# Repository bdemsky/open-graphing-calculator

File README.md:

# Open Graphing Calculator

An open-source graphing calculator: an STM32H743 board with a 3.2" IPS touch display, a full symbolic CAS,
2D (textbook) math, graphing, statistics, matrices, solvers, finance, base-n, units and an RPN mode, and a
3D-printed case. The firmware also runs in a macOS simulator and in the browser.

**[Try it in your browser](https://bdemsky.github.io/open-graphing-calculator/)**: the real firmware, compiled
to WebAssembly, nothing to install.

## The board

| Top | Bottom | With Screen |
|---|---|---|
|  |  |  |

The board was designed by Claude, from the block diagram and part choices to the schematic, placement and
routing (with the Freerouting autorouter and its own finishing passes), all generated by scripts in
[`hardware/gen/`](hardware/gen/) into a KiCad project
([`hardware/kicad/`](hardware/kicad/)). The three boards built so far worked on first power-up, with no
rework. Above, a rev A board as it comes from JLCPCB, still with its panel rails. The
top carries the MCU, the SDRAM, the display connector, the microSD socket, USB-C, the debug headers and the 50
key switches; the bottom, the decoupling capacitors and the two holders for the four AAA cells. On the right,
the first power-up with the display taped on.

## Try it in your browser

**[Open the calculator](https://bdemsky.github.io/open-graphing-calculator/)** (GitHub Pages; with every
module installed, so the full CAS, the manual, animation and the rest are there). Click the keys or type on
your keyboard; the shortcuts are listed under the calculator. Some things to try:

- Type `integrate(x^2*exp(x),x)` and press Enter: the antiderivative, in textbook form.
- `sum(1/k^2,k,1,inf)` gives π²/6; `solve(x^3-6*x^2+11*x-6=0,x)` gives [1,2,3]; `factor(x^4-1)`.
- F1 (graph), type `sin(x)`, F5: a graph cell in the notebook. ENTER on it opens the full graph screen
  (trace, zoom, CALC).
- F1 (graph), F1 again (3D), type `4*sin(x)*cos(y)`, F5: a 3D surface. ENTER opens it; F3 (view) has
  colour by height, contours and a contour map.
- SHIFT then MENU opens the built-in manual for the screen you are on.

The page is [`firmware/web/dist/calculator.html`](firmware/web/dist/calculator.html), one self-contained
file: download it (Raw, then save) to run it offline in any modern browser; it needs no server and no
network. `make web` in `firmware/` rebuilds it ([`firmware/README.md`](firmware/README.md), "Web
simulator"). The page leaves out the Python module, which runs only on the calculator and the simulator.

## Build your own

One calculator is a 4-layer board assembled by JLCPCB, a display, four AAA cells and a 3D-printed PETG case.
Nothing on the board is hand-soldered. Allow about three weeks for parts (the boards and the display both
ship from China) and a weekend for printing and assembly.

| Step | What | Guide |
|---|---|---|
| 1. Order the boards | Upload `hardware/fab/` to JLCPCB: Gerbers, BOM and pick-and-place, PCB and assembly in one order. Use the files exactly as committed: they are the rev A files the working boards were built from. About $30 a board beyond the order's fixed costs; five is a good batch. | [`hardware/ORDER.md`](hardware/ORDER.md) §1 |
| 2. Order the rest | The display (EastRising ER-TFT032IPS-3.2 with the capacitive touch panel, from BuyDisplay), a Raspberry Pi Debug Probe (optional, for debugging), M2 × 3 mm heat-set inserts, M2 × 16 mm screws, AAA cells, PETG filament (white, beige, black), and the face-artwork supplies. | [`hardware/ORDER.md`](hardware/ORDER.md) §2–4 |
| 3. Bring up the board | Inspect it, power it from a current-limited bench supply, flash the bring-up image and run its self-test, then flash the calculator. The prebuilt images are in `firmware/release/`; you don't need to build the firmware. | [`hardware/BRINGUP.md`](hardware/BRINGUP.md), [`firmware/release/FLASHING.md`](firmware/release/FLASHING.md) |
| 4. Print the case | Front, back, battery door and 50 loose keys with inlaid legends. An earlier version was printed and assembled on a 0.4 mm nozzle in PETG; the current shells (no key-mat pegs, corner catches) have not been printed yet. | [`enclosure/README.md`](enclosure/README.md) |
| 5. Assemble | Face artwork (optional), heat-set inserts, keys, display, board, back. | [`enclosure/README.md`](enclosure/README.md) |

You need a soldering iron (for the heat-set inserts), a bench power supply with a current limit, and a
printer that can pause for a filament change (for the key legends). The first flash goes over the board's
USB-C port with dfu-util (ROM bootloader) or over SWD with the Debug Probe and OpenOCD; both are in
`FLASHING.md`.

## What's here

| Directory | Contents |
|---|---|
| [`firmware/`](firmware/README.md) | Firmware, CAS, simulators, help manual, tests, release images. The keyboard layout is [`firmware/keys/layout.py`](firmware/keys/layout.py). |
| [`hardware/`](hardware/ARCHITECTURE.md) | The PCB: the as-built rev A KiCad files and fab outputs, the Python generators, ordering and bring-up guides. |
| [`enclosure/`](enclosure/README.md) | The case, keys and battery door (build123d), slicing scripts, face artwork, print and assembly instructions. |

The keyboard has five soft keys under the display, whose labels change with the screen, and SHIFT and ALPHA
layers printed above the keys. Every key is described once in `firmware/keys/layout.py`, which generates the
firmware key map, the case legends, the web simulator and the key documentation.

## License

MIT ([`LICENSE`](LICENSE)) for everything in this repository (firmware, CAS, tools, the KiCad
design and its generators, the case), except the third-party code and data bundled in
[`firmware/third_party/`](firmware/third_party/README.md) (MicroPython, TinyUSB, CMSIS, KaTeX, the X11
fonts, Kconfiglib), each under its own license in its folder.

The KiCad library has footprints but no 3D models, except the battery holder's (the case's door
check uses it). KiCad opens, checks and exports Gerbers without them; only the 3D viewer shows
bare footprints.

Designed by Claude.

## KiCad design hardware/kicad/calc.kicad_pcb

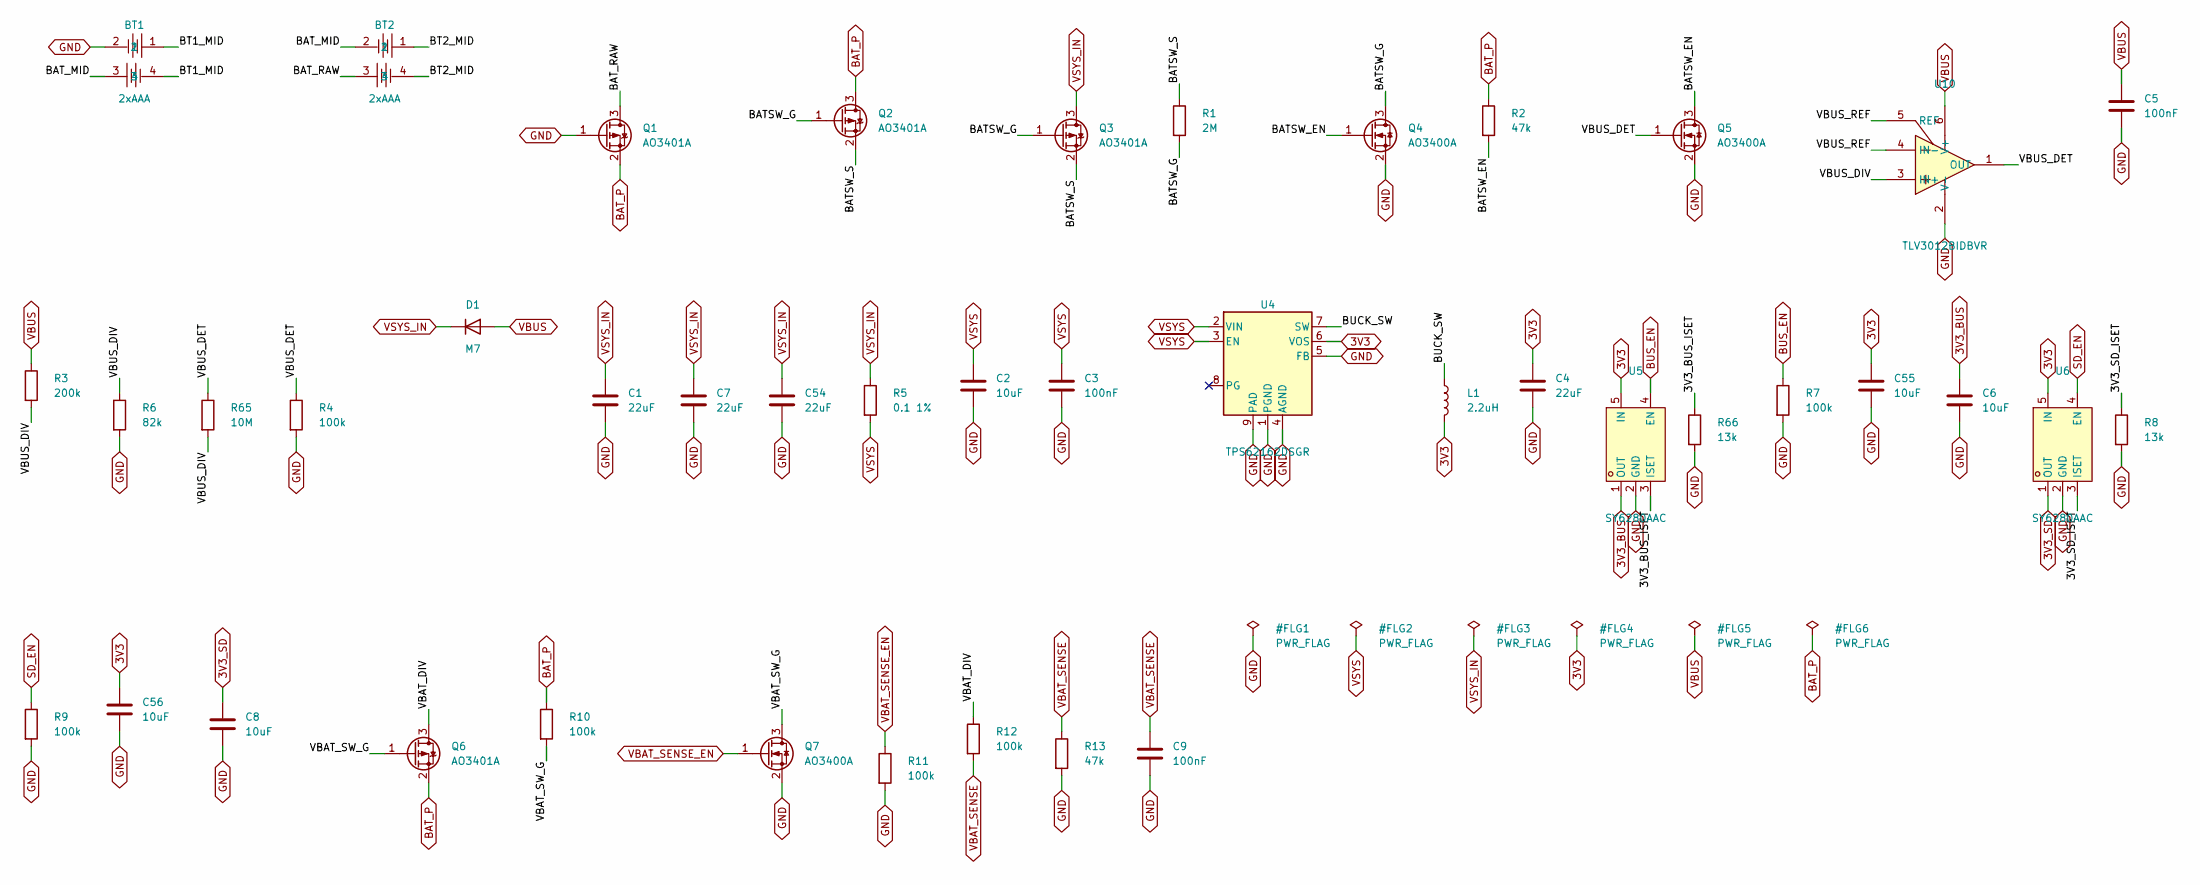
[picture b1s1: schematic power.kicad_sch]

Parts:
BT1, BT2: 2xAAA; BAT-SMD_BH-AAA-B5AA001; LCSC C964881
C1, C4, C7, C54: 22uF; C_0805_2012Metric; LCSC C45783
C2: 10uF; C_0805_2012Metric; LCSC C15850
C3, C5, C9: 100nF; C_0402_1005Metric; LCSC C307331
C6, C8, C55, C56: 10uF; C_0603_1608Metric; LCSC C19702
D1: M7; D_SMA; LCSC C95872
L1: 2.2uH; L_1008_2520Metric; MPN FTC252012S2R2MBCA; LCSC C5832372
Q1, Q2, Q3, Q6: AO3401A; SOT-23; LCSC C15127
Q4, Q5, Q7: AO3400A; SOT-23; LCSC C20917
R1: 2M; R_0603_1608Metric; LCSC C22976
R2, R13: 47k; R_0402_1005Metric; LCSC C25792
R3: 200k; R_0402_1005Metric; LCSC C25764
R4, R7, R9, R10, R11, R12: 100k; R_0402_1005Metric; LCSC C25741
R5: 0.1 1%; R_2512_6332Metric; MPN RLP25FEER100; LCSC C160587
R6: 82k; R_0603_1608Metric; LCSC C23254
R8, R66: 13k; R_0603_1608Metric; LCSC C22797
R65: 10M; R_0603_1608Metric; LCSC C7250
U4: TPS62162DSGR; Texas_DSG0008A_WSON-8-1EP_2x2mm_P0.5mm_EP0.9x1.6mm; LCSC C40256
U5, U6: SY6280AAC; SOT-23-5_L3.0-W1.7-P0.95-LS2.8-BL; LCSC C55136
U10: TLV3012BIDBVR; SOT-23-6_L2.9-W1.7-P0.95-LS2.8-BL; LCSC C20345924

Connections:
3V3: C4.1, C55.1, C56.1, L1.2, U4.6 (VOS), U5.5 (IN), U6.5 (IN); also elsewhere on the board
3V3_BUS: C6.1, U5.1 (OUT); also elsewhere on the board
3V3_SD: C8.1, U6.1 (OUT); also elsewhere on the board
/Power/3V3_BUS_ISET: R66.1, U5.3 (ISET)
/Power/3V3_SD_ISET: R8.1, U6.3 (ISET)
/Power/BATSW_EN: Q4.1 (G), Q5.3 (D), R2.2
/Power/BATSW_G: Q2.1 (G), Q3.1 (G), Q4.3 (D), R1.2
/Power/BATSW_S: Q2.2 (S), Q3.2 (S), R1.1
/Power/BAT_MID: BT1.3, BT2.2
/Power/BAT_RAW: BT2.3, Q1.3 (D)
/Power/BT1_MID: BT1.1, BT1.4
/Power/BT2_MID: BT2.1, BT2.4
/Power/BUCK_SW: L1.1, U4.7 (SW)
/Power/VBAT_DIV: Q6.3 (D), R12.1
/Power/VBAT_SW_G: Q6.1 (G), Q7.3 (D), R10.2
/Power/VBUS_DET: Q5.1 (G), R4.1, R65.1, U10.1 (OUT)
/Power/VBUS_DIV: R3.2, R6.1, R65.2, U10.3 (IN+)
/Power/VBUS_REF: U10.4 (IN-), U10.5 (REF)
BAT_P: Q1.2 (S), Q2.3 (D), Q6.2 (S), R2.1, R10.1; also elsewhere on the board
BUS_EN: R7.1, U5.4 (EN); also elsewhere on the board
GND: BT1.2, C1.2, C2.2, C3.2, C4.2, C5.2, C6.2, C7.2, C8.2, C9.2, C54.2, C55.2, C56.2, Q1.1 (G), Q4.2 (S), Q5.2 (S), Q7.2 (S), R4.2, R6.2, R7.2, R8.2, R9.2, R11.2, R13.2, R66.2, U4.1 (PGND), U4.4 (AGND), U4.5 (FB), U4.9 (PAD), U5.2 (GND), U6.2 (GND), U10.2 (V-); also elsewhere on the board
SD_EN: R9.1, U6.4 (EN); also elsewhere on the board
VBAT_SENSE: C9.1, R12.2, R13.1; also elsewhere on the board
VBAT_SENSE_EN: Q7.1 (G), R11.1; also elsewhere on the board
VBUS: C5.1, D1.2 (A), R3.1, U10.6 (V+); also elsewhere on the board
VSYS: C2.1, C3.1, R5.2, U4.2 (VIN), U4.3 (EN); also elsewhere on the board
VSYS_IN: C1.1, C7.1, C54.1, D1.1 (K), Q3.3 (D), R5.1; also elsewhere on the board

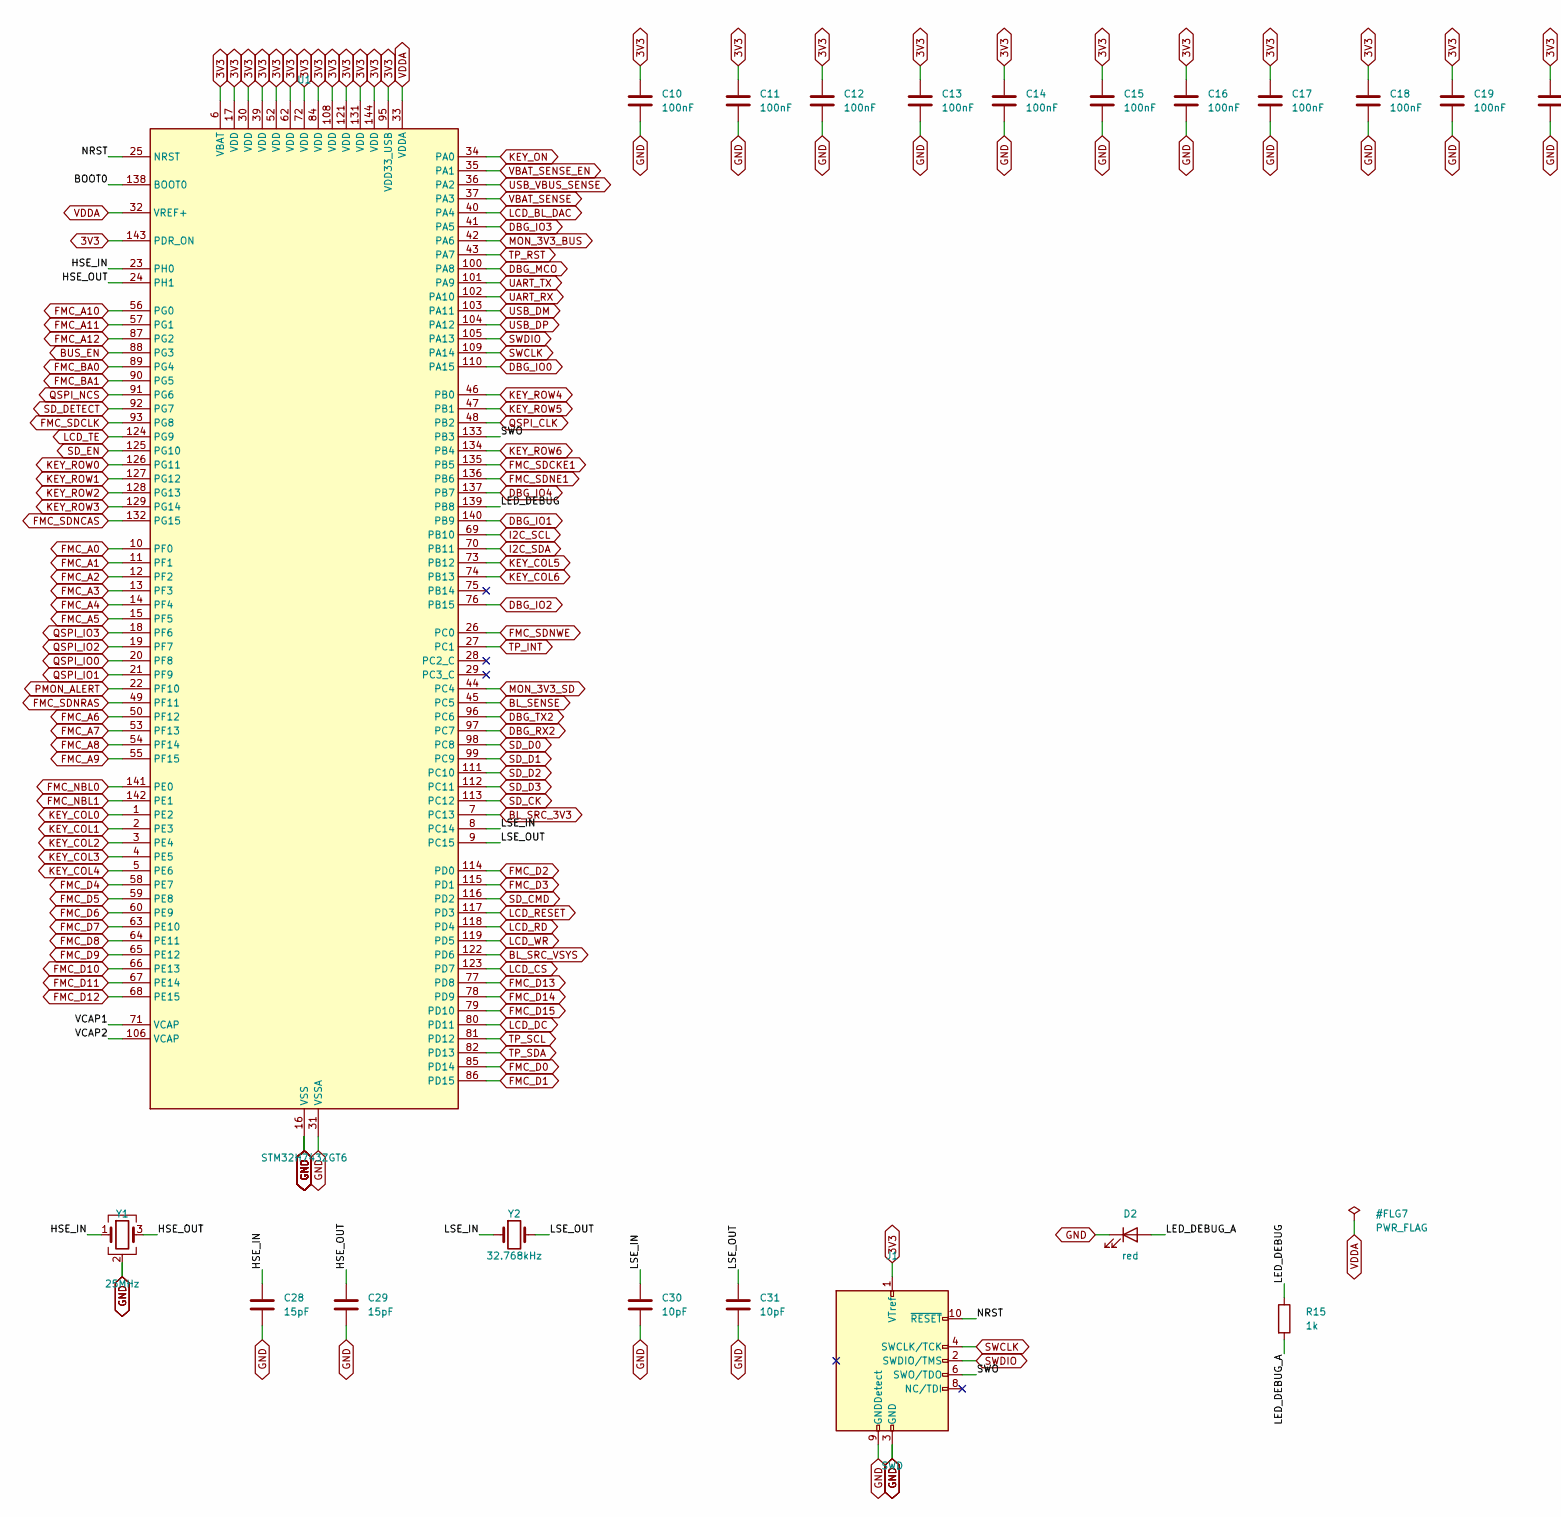
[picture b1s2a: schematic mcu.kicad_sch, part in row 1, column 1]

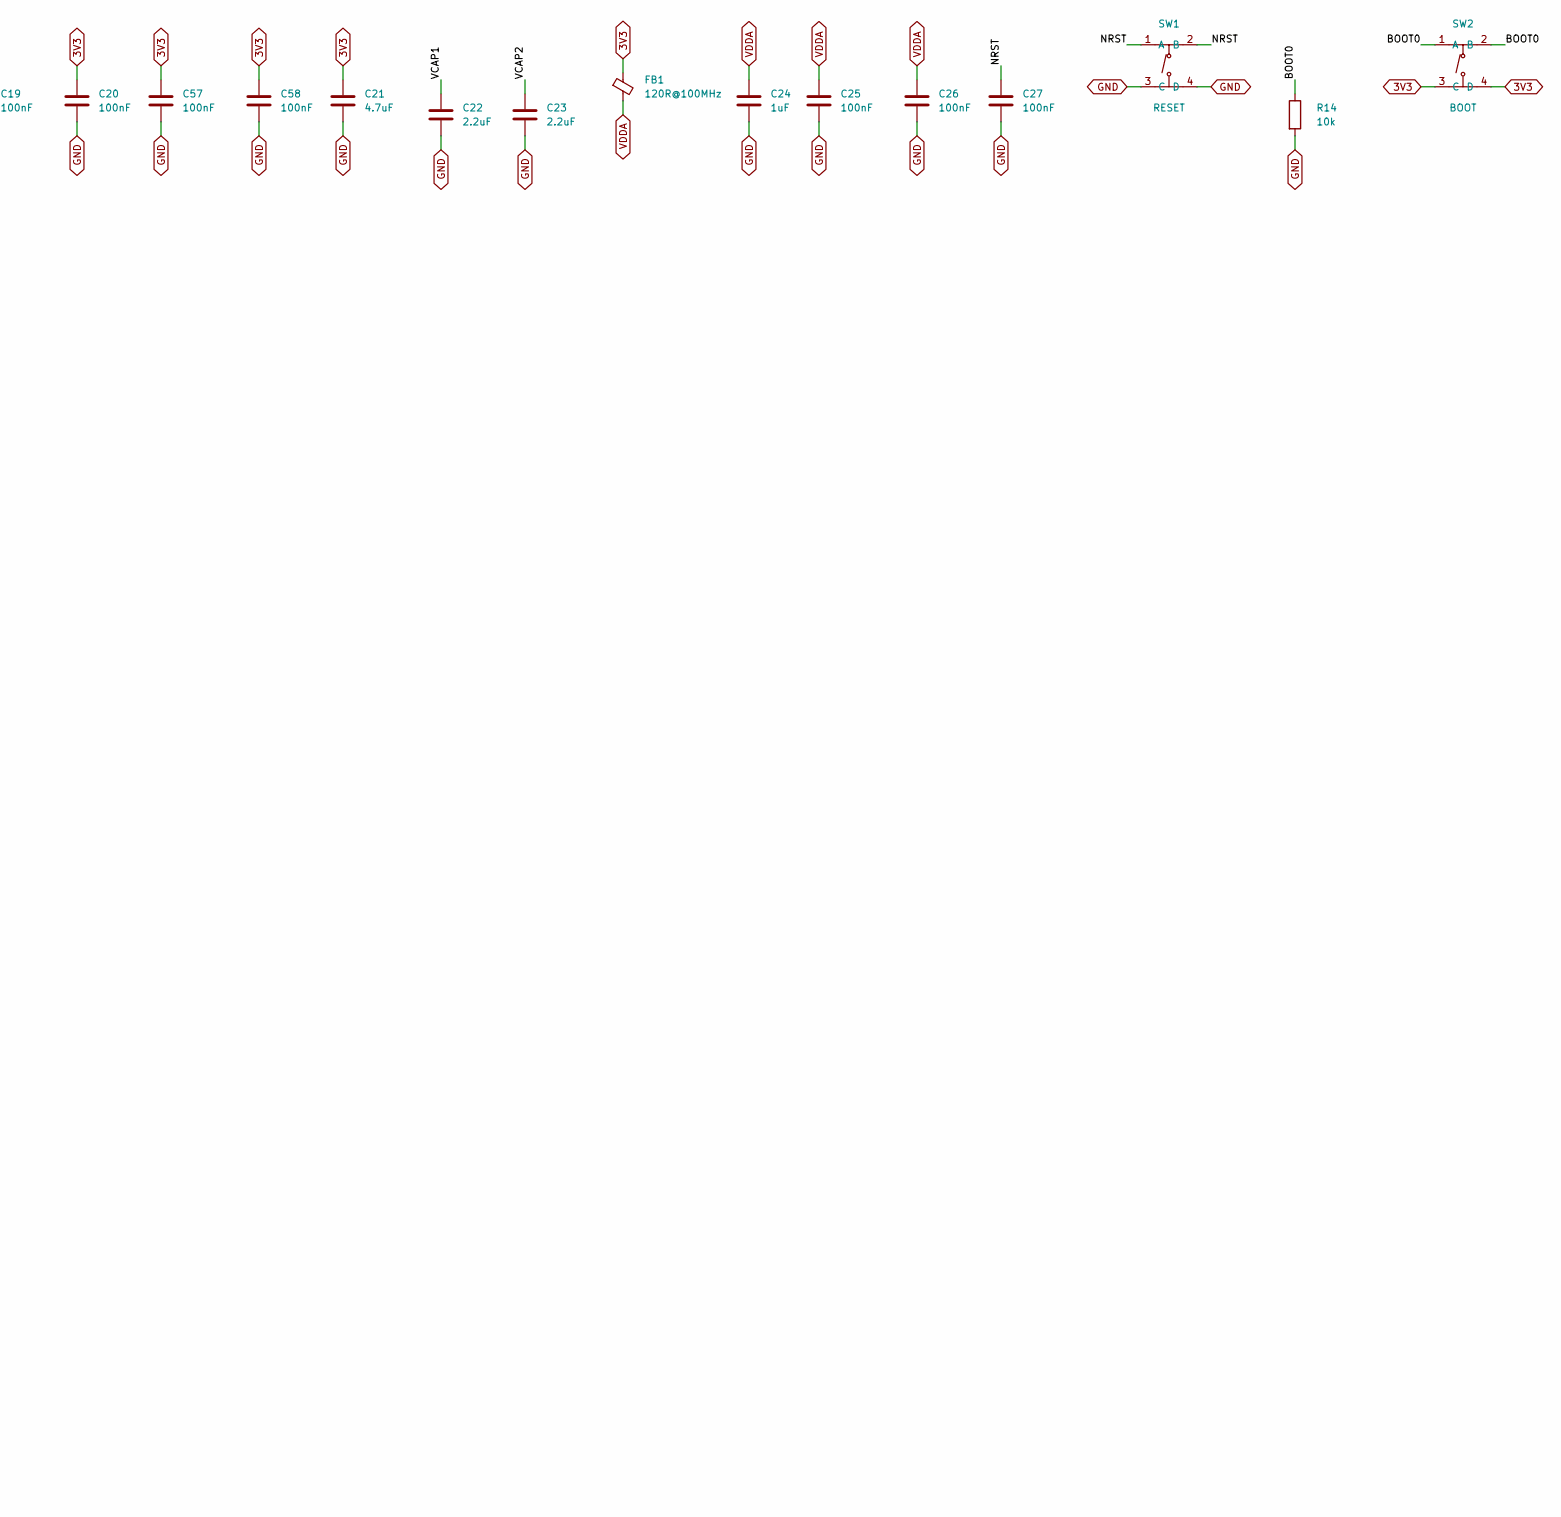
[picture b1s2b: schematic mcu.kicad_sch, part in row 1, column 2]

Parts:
C10, C11, C12, C13, C14, C15, C16, C17, C18, C19, C20, C25, C26, C27, C57, C58: 100nF; C_0402_1005Metric; LCSC C307331
C21: 4.7uF; C_0603_1608Metric; LCSC C19666
C22, C23: 2.2uF; C_0402_1005Metric; LCSC C12530
C24: 1uF; C_0402_1005Metric; LCSC C52923
C28, C29: 15pF; C_0402_1005Metric; LCSC C1548
C30, C31: 10pF; C_0402_1005Metric; LCSC C32949
D2: red; LED_0603_1608Metric; MPN KT-0603R; LCSC C2286
FB1: 120R@100MHz; L_0603_1608Metric; LCSC C14709
J1: SWD; PinHeader_2x05_P1.27mm_Vertical; LCSC C22438120
R14: 10k; R_0402_1005Metric; LCSC C25744
R15: 1k; R_0402_1005Metric; LCSC C11702
SW1: RESET; SW-SMD_4P-L5.1-W5.1-P3.70-LS6.5-TL_H1.5; LCSC C318884
SW2: BOOT; SW-SMD_4P-L5.1-W5.1-P3.70-LS6.5-TL_H1.5; LCSC C318884
U1: STM32H743ZGT6; LQFP-144_20x20mm_P0.5mm; LCSC C730184
Y1: 25MHz; Crystal_SMD_3225-4Pin_3.2x2.5mm; MPN X322525MOB4SI; LCSC C9006
Y2: 32.768kHz; Crystal_SMD_3215-2Pin_3.2x1.5mm; MPN SC-32S 7pF; LCSC C97604

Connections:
3V3: C10.1, C11.1, C12.1, C13.1, C14.1, C15.1, C16.1, C17.1, C18.1, C19.1, C20.1, C21.1, C57.1, C58.1, FB1.1, J1.1 (VTref), SW2.3 (C), SW2.4 (D), U1.6 (VBAT), U1.17 (VDD), U1.30 (VDD), U1.39 (VDD), U1.52 (VDD), U1.62 (VDD), U1.72 (VDD), U1.84 (VDD), U1.95 (VDD33_USB), U1.108 (VDD), U1.121 (VDD), U1.131 (VDD), U1.143 (PDR_ON), U1.144 (VDD); also elsewhere on the board
/MCU/BOOT0: R14.1, SW2.1 (A), SW2.2 (B), U1.138 (BOOT0)
/MCU/HSE_IN: C28.1, U1.23 (PH0), Y1.1
/MCU/HSE_OUT: C29.1, U1.24 (PH1), Y1.3
/MCU/LED_DEBUG: R15.1, U1.139 (PB8)
/MCU/LED_DEBUG_A: D2.2 (A), R15.2
/MCU/LSE_IN: C30.1, U1.8 (PC14), Y2.1
/MCU/LSE_OUT: C31.1, U1.9 (PC15), Y2.2
/MCU/NRST: C27.1, J1.10 (~RESET), SW1.1 (A), SW1.2 (B), U1.25 (NRST)
/MCU/SWO: J1.6 (SWO/TDO), U1.133 (PB3)
/MCU/VCAP1: C22.1, U1.71 (VCAP)
/MCU/VCAP2: C23.1, U1.106 (VCAP)
BL_SENSE: U1.45 (PC5); also elsewhere on the board
BL_SRC_3V3: U1.7 (PC13); also elsewhere on the board
BL_SRC_VSYS: U1.122 (PD6); also elsewhere on the board
BUS_EN: U1.88 (PG3); also elsewhere on the board
DBG_IO0: U1.110 (PA15); also elsewhere on the board
DBG_IO1: U1.140 (PB9); also elsewhere on the board
DBG_IO2: U1.76 (PB15); also elsewhere on the board
DBG_IO3: U1.41 (PA5); also elsewhere on the board
DBG_IO4: U1.137 (PB7); also elsewhere on the board
DBG_MCO: U1.100 (PA8); also elsewhere on the board
DBG_RX2: U1.97 (PC7); also elsewhere on the board
DBG_TX2: U1.96 (PC6); also elsewhere on the board
FMC_A0: U1.10 (PF0); also elsewhere on the board
FMC_A1: U1.11 (PF1); also elsewhere on the board
FMC_A2: U1.12 (PF2); also elsewhere on the board
FMC_A3: U1.13 (PF3); also elsewhere on the board
FMC_A4: U1.14 (PF4); also elsewhere on the board
FMC_A5: U1.15 (PF5); also elsewhere on the board
FMC_A6: U1.50 (PF12); also elsewhere on the board
FMC_A7: U1.53 (PF13); also elsewhere on the board
FMC_A8: U1.54 (PF14); also elsewhere on the board
FMC_A9: U1.55 (PF15); also elsewhere on the board
FMC_A10: U1.56 (PG0); also elsewhere on the board
FMC_A11: U1.57 (PG1); also elsewhere on the board
FMC_A12: U1.87 (PG2); also elsewhere on the board
FMC_BA0: U1.89 (PG4); also elsewhere on the board
FMC_BA1: U1.90 (PG5); also elsewhere on the board
FMC_D0: U1.85 (PD14); also elsewhere on the board
FMC_D1: U1.86 (PD15); also elsewhere on the board
FMC_D2: U1.114 (PD0); also elsewhere on the board
FMC_D3: U1.115 (PD1); also elsewhere on the board
FMC_D4: U1.58 (PE7); also elsewhere on the board
FMC_D5: U1.59 (PE8); also elsewhere on the board
FMC_D6: U1.60 (PE9); also elsewhere on the board
FMC_D7: U1.63 (PE10); also elsewhere on the board
FMC_D8: U1.64 (PE11); also elsewhere on the board
FMC_D9: U1.65 (PE12); also elsewhere on the board
FMC_D10: U1.66 (PE13); also elsewhere on the board
FMC_D11: U1.67 (PE14); also elsewhere on the board
FMC_D12: U1.68 (PE15); also elsewhere on the board
FMC_D13: U1.77 (PD8); also elsewhere on the board
FMC_D14: U1.78 (PD9); also elsewhere on the board
FMC_D15: U1.79 (PD10); also elsewhere on the board
FMC_NBL0: U1.141 (PE0); also elsewhere on the board
FMC_NBL1: U1.142 (PE1); also elsewhere on the board
FMC_SDCKE1: U1.135 (PB5); also elsewhere on the board
FMC_SDCLK: U1.93 (PG8); also elsewhere on the board
FMC_SDNCAS: U1.132 (PG15); also elsewhere on the board
FMC_SDNE1: U1.136 (PB6); also elsewhere on the board
FMC_SDNRAS: U1.49 (PF11); also elsewhere on the board
FMC_SDNWE: U1.26 (PC0); also elsewhere on the board
GND: C10.2, C11.2, C12.2, C13.2, C14.2, C15.2, C16.2, C17.2, C18.2, C19.2, C20.2, C21.2, C22.2, C23.2, C24.2, C25.2, C26.2, C27.2, C28.2, C29.2, C30.2, C31.2, C57.2, C58.2, D2.1 (K), J1.3 (GND), J1.5 (GND), J1.9 (GNDDetect), R14.2, SW1.3 (C), SW1.4 (D), U1.16 (VSS), U1.31 (VSSA), U1.38 (VSS), U1.51 (VSS), U1.61 (VSS), U1.83 (VSS), U1.94 (VSS), U1.107 (VSS), U1.120 (VSS), U1.130 (VSS), Y1.2 (G), Y1.4 (G); also elsewhere on the board
I2C_SCL: U1.69 (PB10); also elsewhere on the board
I2C_SDA: U1.70 (PB11); also elsewhere on the board
KEY_COL0: U1.1 (PE2); also elsewhere on the board
KEY_COL1: U1.2 (PE3); also elsewhere on the board
KEY_COL2: U1.3 (PE4); also elsewhere on the board
KEY_COL3: U1.4 (PE5); also elsewhere on the board
KEY_COL4: U1.5 (PE6); also elsewhere on the board
KEY_COL5: U1.73 (PB12); also elsewhere on the board
KEY_COL6: U1.74 (PB13); also elsewhere on the board
KEY_ON: U1.34 (PA0); also elsewhere on the board
KEY_ROW0: U1.126 (PG11); also elsewhere on the board
KEY_ROW1: U1.127 (PG12); also elsewhere on the board
KEY_ROW2: U1.128 (PG13); also elsewhere on the board
KEY_ROW3: U1.129 (PG14); also elsewhere on the board
KEY_ROW4: U1.46 (PB0); also elsewhere on the board
KEY_ROW5: U1.47 (PB1); also elsewhere on the board
KEY_ROW6: U1.134 (PB4); also elsewhere on the board
LCD_BL_DAC: U1.40 (PA4); also elsewhere on the board
LCD_CS: U1.123 (PD7); also elsewhere on the board
LCD_DC: U1.80 (PD11); also elsewhere on the board
LCD_RD: U1.118 (PD4); also elsewhere on the board
LCD_RESET: U1.117 (PD3); also elsewhere on the board
LCD_TE: U1.124 (PG9); also elsewhere on the board
LCD_WR: U1.119 (PD5); also elsewhere on the board
MON_3V3_BUS: U1.42 (PA6); also elsewhere on the board
MON_3V3_SD: U1.44 (PC4); also elsewhere on the board
PMON_ALERT: U1.22 (PF10); also elsewhere on the board
QSPI_CLK: U1.48 (PB2); also elsewhere on the board
QSPI_IO0: U1.20 (PF8); also elsewhere on the board
QSPI_IO1: U1.21 (PF9); also elsewhere on the board
QSPI_IO2: U1.19 (PF7); also elsewhere on the board
QSPI_IO3: U1.18 (PF6); also elsewhere on the board
QSPI_NCS: U1.91 (PG6); also elsewhere on the board
SD_CK: U1.113 (PC12); also elsewhere on the board
SD_CMD: U1.116 (PD2); also elsewhere on the board
SD_D0: U1.98 (PC8); also elsewhere on the board
SD_D1: U1.99 (PC9); also elsewhere on the board
SD_D2: U1.111 (PC10); also elsewhere on the board
SD_D3: U1.112 (PC11); also elsewhere on the board
SD_DETECT: U1.92 (PG7); also elsewhere on the board
SD_EN: U1.125 (PG10); also elsewhere on the board
SWCLK: J1.4 (SWCLK/TCK), U1.109 (PA14); also elsewhere on the board
SWDIO: J1.2 (SWDIO/TMS), U1.105 (PA13); also elsewhere on the board
TP_INT: U1.27 (PC1); also elsewhere on the board
TP_RST: U1.43 (PA7); also elsewhere on the board
TP_SCL: U1.81 (PD12); also elsewhere on the board
TP_SDA: U1.82 (PD13); also elsewhere on the board
UART_RX: U1.102 (PA10); also elsewhere on the board
UART_TX: U1.101 (PA9); also elsewhere on the board
USB_DM: U1.103 (PA11); also elsewhere on the board
USB_DP: U1.104 (PA12); also elsewhere on the board
USB_VBUS_SENSE: U1.36 (PA2); also elsewhere on the board
VBAT_SENSE: U1.37 (PA3); also elsewhere on the board
VBAT_SENSE_EN: U1.35 (PA1); also elsewhere on the board
VDDA: C24.1, C25.1, C26.1, FB1.2, U1.32 (VREF+), U1.33 (VDDA); also elsewhere on the board

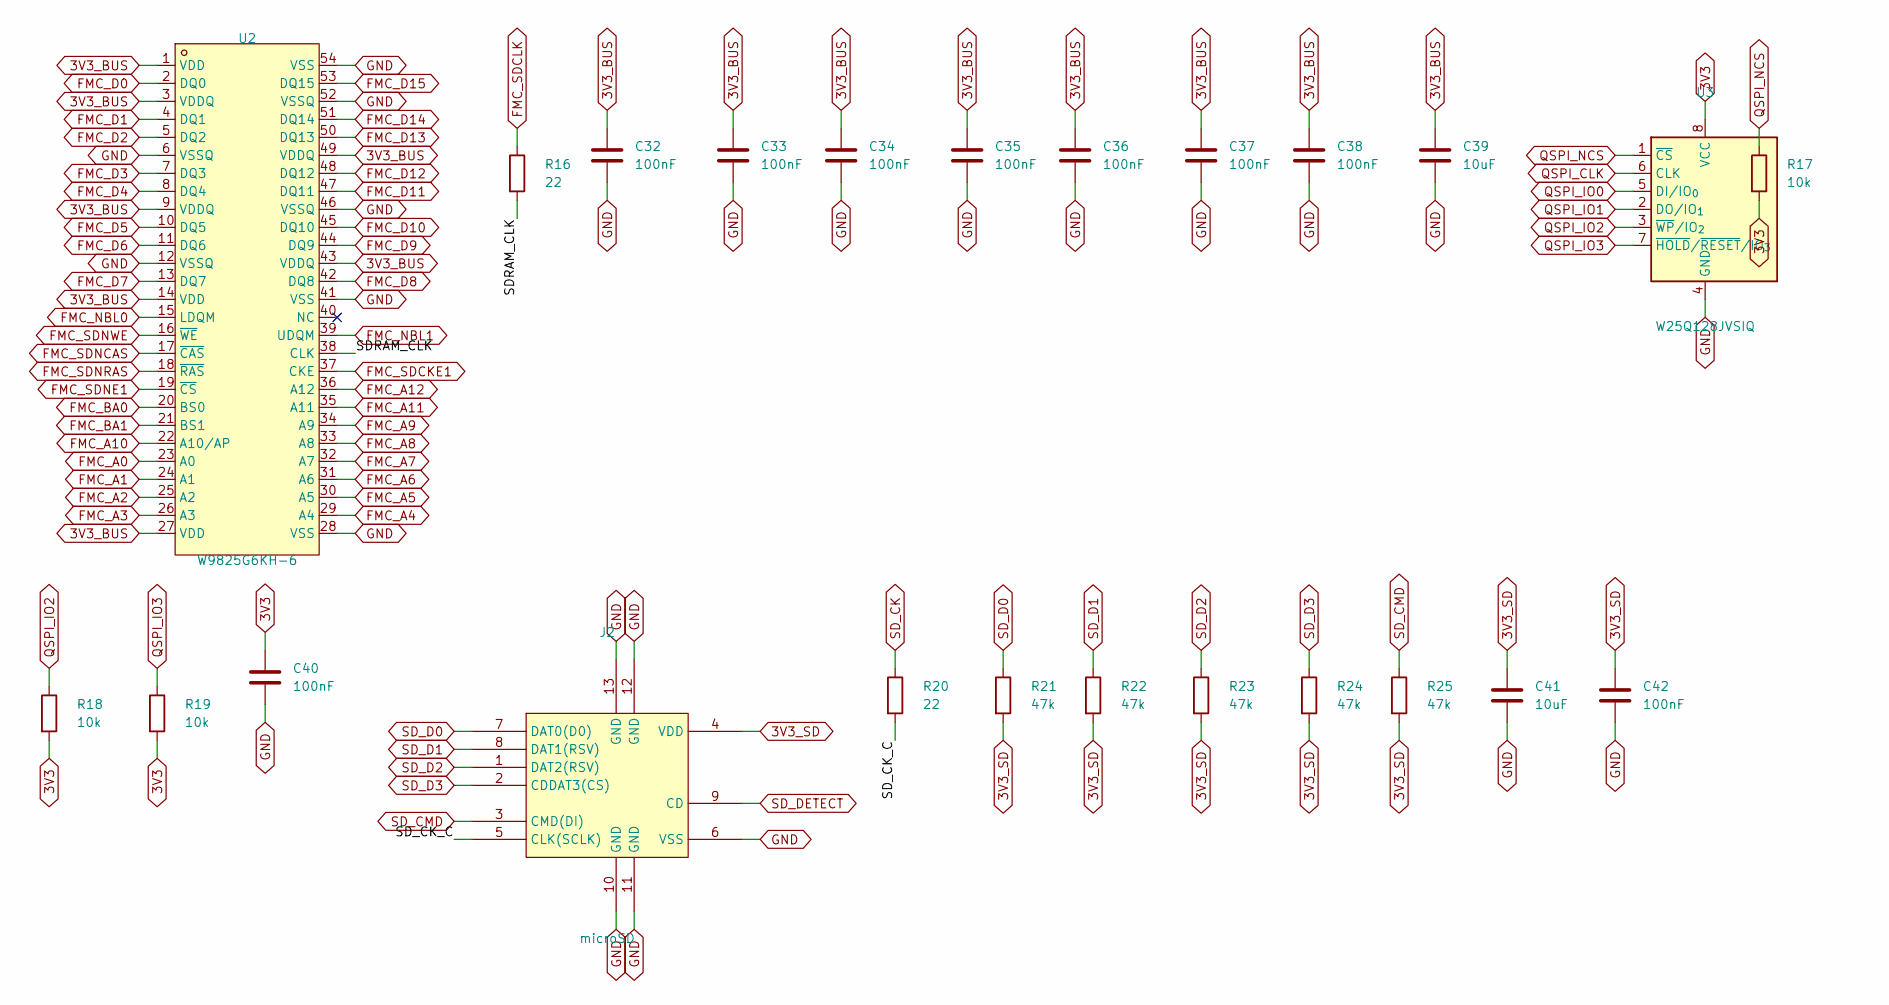
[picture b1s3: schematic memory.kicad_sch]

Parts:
C32, C33, C34, C35, C36, C37, C38, C40, C42: 100nF; C_0402_1005Metric; LCSC C307331
C39, C41: 10uF; C_0603_1608Metric; LCSC C19702
J2: microSD; TF-SMD_TF-01A; LCSC C91145
R16, R20: 22; R_0402_1005Metric; LCSC C25092
R17, R18, R19: 10k; R_0402_1005Metric; LCSC C25744
R21, R22, R23, R24, R25: 47k; R_0402_1005Metric; LCSC C25792
U2: W9825G6KH-6; TSOP-54_L22.2-W10.2-P0.80-LS11.8-BL; LCSC C62246
U3: W25Q128JVSIQ; SOIC-8_5.3x5.3mm_P1.27mm; LCSC C97521

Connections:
3V3: C40.1, R17.2, R18.2, R19.2, U3.8 (VCC); also elsewhere on the board
3V3_BUS: C32.1, C33.1, C34.1, C35.1, C36.1, C37.1, C38.1, C39.1, U2.1 (VDD), U2.3 (VDDQ), U2.9 (VDDQ), U2.14 (VDD), U2.27 (VDD), U2.43 (VDDQ), U2.49 (VDDQ); also elsewhere on the board
3V3_SD: C41.1, C42.1, J2.4 (VDD), R21.2, R22.2, R23.2, R24.2, R25.2; also elsewhere on the board
/Memory/SDRAM_CLK: R16.2, U2.38 (CLK)
/Memory/SD_CK_C: J2.5 (CLK(SCLK)), R20.2
FMC_A0: U2.23 (A0); also elsewhere on the board
FMC_A1: U2.24 (A1); also elsewhere on the board
FMC_A2: U2.25 (A2); also elsewhere on the board
FMC_A3: U2.26 (A3); also elsewhere on the board
FMC_A4: U2.29 (A4); also elsewhere on the board
FMC_A5: U2.30 (A5); also elsewhere on the board
FMC_A6: U2.31 (A6); also elsewhere on the board
FMC_A7: U2.32 (A7); also elsewhere on the board
FMC_A8: U2.33 (A8); also elsewhere on the board
FMC_A9: U2.34 (A9); also elsewhere on the board
FMC_A10: U2.22 (A10/AP); also elsewhere on the board
FMC_A11: U2.35 (A11); also elsewhere on the board
FMC_A12: U2.36 (A12); also elsewhere on the board
FMC_BA0: U2.20 (BS0); also elsewhere on the board
FMC_BA1: U2.21 (BS1); also elsewhere on the board
FMC_D0: U2.2 (DQ0); also elsewhere on the board
FMC_D1: U2.4 (DQ1); also elsewhere on the board
FMC_D2: U2.5 (DQ2); also elsewhere on the board
FMC_D3: U2.7 (DQ3); also elsewhere on the board
FMC_D4: U2.8 (DQ4); also elsewhere on the board
FMC_D5: U2.10 (DQ5); also elsewhere on the board
FMC_D6: U2.11 (DQ6); also elsewhere on the board
FMC_D7: U2.13 (DQ7); also elsewhere on the board
FMC_D8: U2.42 (DQ8); also elsewhere on the board
FMC_D9: U2.44 (DQ9); also elsewhere on the board
FMC_D10: U2.45 (DQ10); also elsewhere on the board
FMC_D11: U2.47 (DQ11); also elsewhere on the board
FMC_D12: U2.48 (DQ12); also elsewhere on the board
FMC_D13: U2.50 (DQ13); also elsewhere on the board
FMC_D14: U2.51 (DQ14); also elsewhere on the board
FMC_D15: U2.53 (DQ15); also elsewhere on the board
FMC_NBL0: U2.15 (LDQM); also elsewhere on the board
FMC_NBL1: U2.39 (UDQM); also elsewhere on the board
FMC_SDCKE1: U2.37 (CKE); also elsewhere on the board
FMC_SDCLK: R16.1; also elsewhere on the board
FMC_SDNCAS: U2.17 (~CAS); also elsewhere on the board
FMC_SDNE1: U2.19 (~CS); also elsewhere on the board
FMC_SDNRAS: U2.18 (~RAS); also elsewhere on the board
FMC_SDNWE: U2.16 (~WE); also elsewhere on the board
GND: C32.2, C33.2, C34.2, C35.2, C36.2, C37.2, C38.2, C39.2, C40.2, C41.2, C42.2, J2.6 (VSS), J2.10 (GND), J2.11 (GND), J2.12 (GND), J2.13 (GND), U2.6 (VSSQ), U2.12 (VSSQ), U2.28 (VSS), U2.41 (VSS), U2.46 (VSSQ), U2.52 (VSSQ), U2.54 (VSS), U3.4 (GND); also elsewhere on the board
QSPI_CLK: U3.6 (CLK); also elsewhere on the board
QSPI_IO0: U3.5 (DI/IO_{0}); also elsewhere on the board
QSPI_IO1: U3.2 (DO/IO_{1}); also elsewhere on the board
QSPI_IO2: R18.1, U3.3 (~WP/IO_{2}); also elsewhere on the board
QSPI_IO3: R19.1, U3.7 (~HOLD/~RESET/IO_{3}); also elsewhere on the board
QSPI_NCS: R17.1, U3.1 (~CS); also elsewhere on the board
SD_CK: R20.1; also elsewhere on the board
SD_CMD: J2.3 (CMD(DI)), R25.1; also elsewhere on the board
SD_D0: J2.7 (DAT0(D0)), R21.1; also elsewhere on the board
SD_D1: J2.8 (DAT1(RSV)), R22.1; also elsewhere on the board
SD_D2: J2.1 (DAT2(RSV)), R23.1; also elsewhere on the board
SD_D3: J2.2 (CDDAT3(CS)), R24.1; also elsewhere on the board
SD_DETECT: J2.9 (CD); also elsewhere on the board
